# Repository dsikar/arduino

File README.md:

LCD multinode proof of concept
==============

Connect an LCD to a master node, plus a 3 node selector resistor ladder, to a slave node hooked up to a thermistor (LM35).  

This proof-of-concept builds on the Arduino Due to an Arduino Uno I<sup>2</sup>C protocol communication as described in this other GitHub [repository](https://github.com/dsikar/due-uno-i2c). A real life implementation can be found [here](https://github.com/dsikar/arduino/tree/master/lcd-multinode-master-pidx3).

Now there is an LCD plus a resistor ladder added to the master node and a thermistor added to the slave node. Temperature is set on the master node and, while no PID over is hooked up, read from the slave node.

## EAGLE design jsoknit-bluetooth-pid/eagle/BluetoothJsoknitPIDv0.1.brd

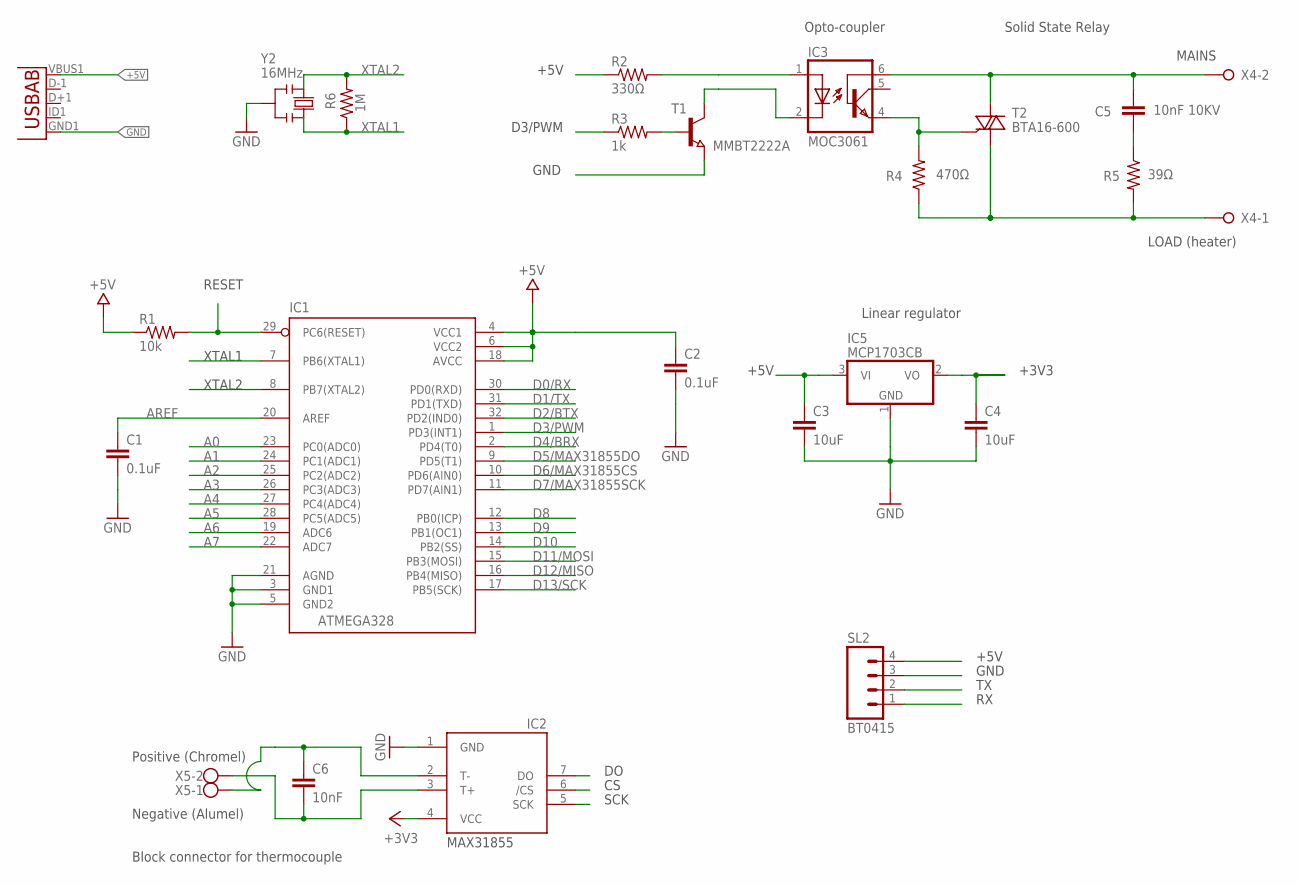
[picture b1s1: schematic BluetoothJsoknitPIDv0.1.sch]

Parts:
C1, C2: 0.1uF; C0805
C3, C4: 10uF; C0805
C5: 10nF 10KV; C050-025X075
C6: 10nF; C0805
IC1: ATMEGA328; QFP032
IC2: MAX6675; SO08
IC3: MOC3061; DIL6-SMD
IC5: MCP1703CB; SOT23
R1: 10k; M0805
R2: 330Ω; M0805
R3: 1k; M0805
R4: 470Ω; 0207/10
R5: 39Ω; 0207/10
R6: 1M; M0805
SL2: BT0415; 04P
T1: MMBT2222A; SOT23
T2: BTA16-600; TO220BV
U$4: USB-AB""; USB-AB-MICRO-SMD_V02_BOSS
X4: W237-02P; W237-132
X5: W237-102
Y2: 16MHz; RESONATOR

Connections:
+3V3: C4.1, IC2.4 (VCC), IC5.2 (VO)
+5V: C2.1, C3.1, IC1.4 (VCC1), IC1.6 (VCC2), IC1.18 (AVCC), IC5.3 (VI), R1.1, R2.1, SL2.4, U$4.VBUS1 (VBUS)
A0: IC1.23 (PC0(ADC0))
A1: IC1.24 (PC1(ADC1))
A2: IC1.25 (PC2(ADC2))
A3: IC1.26 (PC3(ADC3))
A4: IC1.27 (PC4(ADC4))
A5: IC1.28 (PC5(ADC5))
A6: IC1.19 (ADC6)
A7: IC1.22 (ADC7)
AREF: C1.1, IC1.20 (AREF)
D0/RX: IC1.30 (PD0(RXD))
D1/TX: IC1.31 (PD1(TXD))
D2/BTX: IC1.32 (PD2(IND0)), SL2.2
D3/PWM: IC1.1 (PD3(INT1)), R3.1
D4/BRX: IC1.2 (PD4(T0)), SL2.1
D5/MAX31855DO: IC1.9 (PD5(T1)), IC2.7 (DO)
D6/MAX31855CS: IC1.10 (PD6(AIN0)), IC2.6 (/CS)
D7/MAX31855SCK: IC1.11 (PD7(AIN1)), IC2.5 (SCK)
D8: IC1.12 (PB0(ICP))
D9: IC1.13 (PB1(OC1))
D10: IC1.14 (PB2(SS))
D11/MOSI: IC1.15 (PB3(MOSI))
D12/MISO: IC1.16 (PB4(MISO))
D13/SCK: IC1.17 (PB5(SCK))
GND: C1.2, C2.2, C3.2, C4.2, IC1.3 (GND1), IC1.5 (GND2), IC1.21 (AGND), IC2.1 (GND), IC5.1 (GND), SL2.3, T1.2 (E), U$4.GND1 (GND), Y2.2
LOAD: R4.1, R5.2, T2.T1 (A1), X4.1
MAINS: C5.1, IC3.6 (BAS), T2.T2 (A2), X4.2
MOC3061PIN4: IC3.4 (EMI), R4.2, T2.G
unnamed: IC3.2 (C), T1.3 (C)
unnamed: R3.2, T1.1 (B)
unnamed: IC3.1 (A), R2.2
unnamed: C5.2, R5.1
RESET: IC1.29 (PC6(RESET)), R1.2
T+: C6.2, IC2.3 (T+), X5.2
T-: C6.1, IC2.2 (T-)
T-1: X5.1
XTAL1: IC1.7 (PB6(XTAL1)), R6.1, Y2.3
XTAL2: IC1.8 (PB7(XTAL2)), R6.2, Y2.1

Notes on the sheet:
XTAL1
XTAL2
+5V
D3/PWM
GND
LOAD (heater)
MAINS
Block connector for thermocouple
SCK
Positive (Chromel)
Negative (Alumel)
+3V3
Opto-coupler
Solid State Relay
Linear regulator
MAX31855
RESET

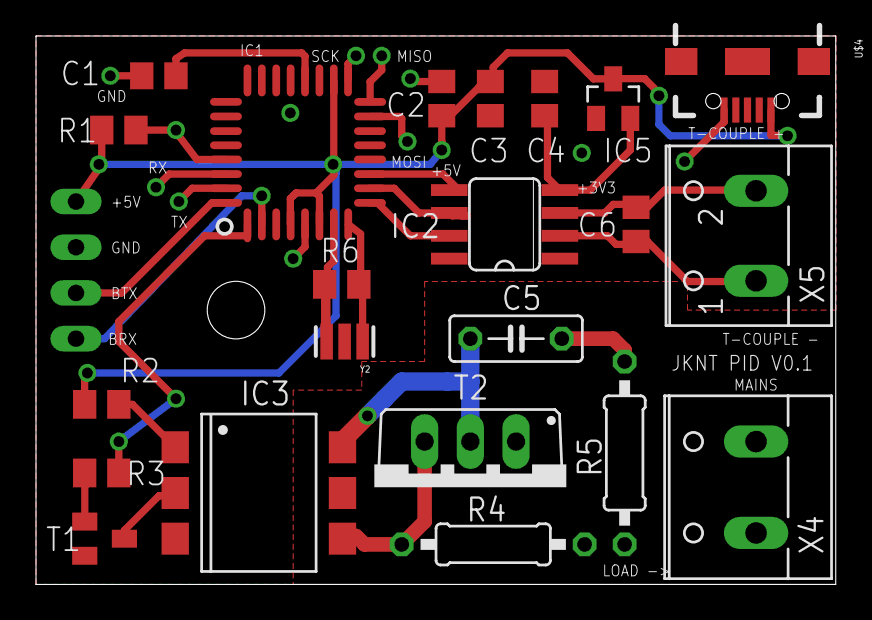
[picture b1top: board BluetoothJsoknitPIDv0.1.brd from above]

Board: 2 copper layers, 44.4 x 30.5 mm, 23 parts (1 on the bottom side), 22 nets.

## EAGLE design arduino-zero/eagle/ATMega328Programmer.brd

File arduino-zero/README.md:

$1 Arduino programmer a.k.a RDNO Zero.
==============

This device provides the following features:  

* Ability to burn a bootloader and upload code to an ATmega328 TQFP-32 device.
* 5 output pins: D0, D1, D11, D12 and D13.  

To burn the bootloader and upload code, [follow these steps] (https://github.com/dsikar/arduino/tree/master/lcd-multinode-master-pidx3#notes-on-configuring-the-arduino-on-a-breadboard), changing the Due board option for Uno, basically turning the ATmega328 TQFP-32 into a feature-limited Uno, hence the name RDNO 0.

Notice that when burning the bootloader, SCK, MOSI, MISO and RESET pins need to be wired. When uploading code, the required pins are RX, TX and RESET. In both cases, Ground and +5V need to be wired.  

Once the code is uploaded, you'll have a very basic Arduino in your hands, and somewhat precarious, given that the chip is secured to board with a crocodile clip, but hey, that is $1's worth of arduino goodness.

The connectors on the board, from left to right, match the SL1 connector in the schematic from top to bottom.

# Gallery

**Burning the bootloader**  
Here we have SCK, MOSI, MISO, RESET, +5V and GND wired    

**Uploading code**  
RX, TX, RESET, +5V and GND wired  

**Blink example**  
SCK, +5V and GND wired, SCK (D13) wired to UNO's D13 to use the on-board LED  

**Bluetooth LED**  
D11, D12, D13, +5V and GND wired, D11 wired to LED, D11 and D12 functioning as RX and TX to [Bluetooth module] (https://github.com/dsikar/jskonit-proof-of-concept)

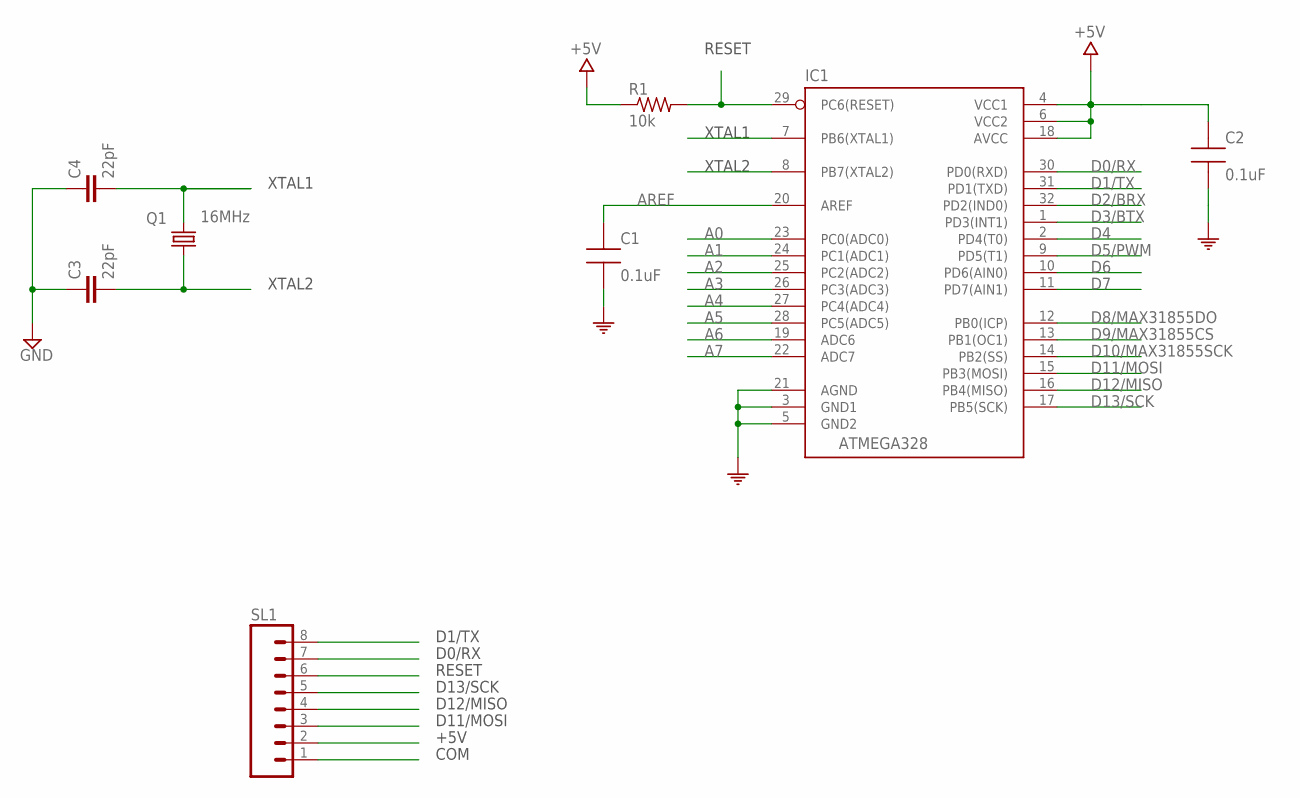
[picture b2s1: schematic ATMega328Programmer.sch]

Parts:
C1, C2: 0.1uF; CAP0805-NP
C3, C4: 22pF; C0805
IC1: ATMEGA328; QFP032
Q1: 16MHz; HC49/S
R1: 10k; M0805
SL1: M08; 08P

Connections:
+5V: C2.1, IC1.4 (VCC1), IC1.6 (VCC2), IC1.18 (AVCC), R1.1, SL1.2
A0: IC1.23 (PC0(ADC0))
A1: IC1.24 (PC1(ADC1))
A2: IC1.25 (PC2(ADC2))
A3: IC1.26 (PC3(ADC3))
A4: IC1.27 (PC4(ADC4))
A5: IC1.28 (PC5(ADC5))
A6: IC1.19 (ADC6)
A7: IC1.22 (ADC7)
AREF: C1.1, IC1.20 (AREF)
COM: C1.2, C2.2, C3.1, C4.1, IC1.3 (GND1), IC1.5 (GND2), IC1.21 (AGND), SL1.1
D0/RX: IC1.30 (PD0(RXD)), SL1.7
D1/TX: IC1.31 (PD1(TXD)), SL1.8
D2/BRX: IC1.32 (PD2(IND0))
D3/BTX: IC1.1 (PD3(INT1))
D4: IC1.2 (PD4(T0))
D5/PWM: IC1.9 (PD5(T1))
D6: IC1.10 (PD6(AIN0))
D7: IC1.11 (PD7(AIN1))
D8/MAX31855DO: IC1.12 (PB0(ICP))
D9/MAX31855CS: IC1.13 (PB1(OC1))
D10/MAX31855SCK: IC1.14 (PB2(SS))
D11/MOSI: IC1.15 (PB3(MOSI)), SL1.3
D12/MISO: IC1.16 (PB4(MISO)), SL1.4
D13/SCK: IC1.17 (PB5(SCK)), SL1.5
RESET: IC1.29 (PC6(RESET)), R1.2, SL1.6
XTAL1: C4.2, IC1.7 (PB6(XTAL1)), Q1.2
XTAL2: C3.2, IC1.8 (PB7(XTAL2)), Q1.1

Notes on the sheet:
XTAL1
XTAL2
RESET
D1/TX
D0/RX
D13/SCK
D12/MISO
D11/MOSI
+5V
COM

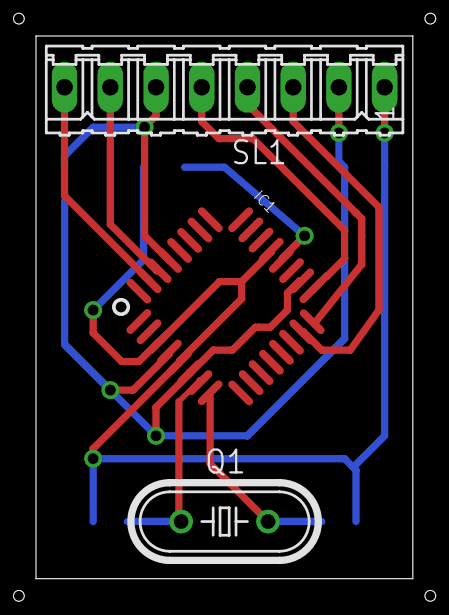
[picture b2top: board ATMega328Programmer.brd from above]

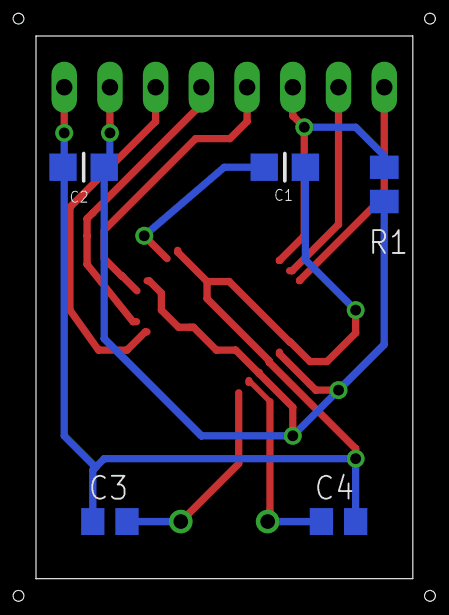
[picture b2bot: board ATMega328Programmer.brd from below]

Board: 2 copper layers, 20.9 x 30.1 mm, 8 parts (5 on the bottom side), 11 nets.

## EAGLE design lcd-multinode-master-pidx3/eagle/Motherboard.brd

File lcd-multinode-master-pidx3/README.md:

LCD master node with breadboard slave node
==============

Now that the Arduino Uno and Due can communicate using the Wire (I2C) library, I'm substituting the Due for an Arduino on a breadboard.  

What we had to start with was:  

Once the Due was swapped, it ended up like this:  

# Notes on configuring the Arduino on a breadboard  

To burn the bootloader and upload sketches to the breadboard Arduino, I followed [these instructions](http://www.arduino.cc/en/Tutorial/ArduinoToBreadboard "http://www.arduino.cc/en/Tutorial/ArduinoToBreadboard") on the arduino.cc website.  

Basically, I wire an Arduino Uno to a breadboard Arduino following this Wiring diagram:  

I worked with two IDEs, versions 1.0.6 and 1.6.4.    

Burning the bootloader threw the error:  

```
(...)
avrdude: Device signature = 0x1e9514
avrdude: Expected signature for ATMEGA328P is 1E 95 0F
         Double check chip, or use -F to override this check.
(...)
```

The error message states that the device signature does not match the expected device signature, as found in configuration file /hardware/tools/avr/etc/avrdude.conf.  
IDE 1.0.6 calls for a change in the last line shown:  

```
#------------------------------------------------------------
# ATmega328P
#------------------------------------------------------------

part
    id			= "m328p";
    desc		= "ATMEGA328P";
    has_debugwire	= yes;
    flash_instr		= 0xB6, 0x01, 0x11;
    eeprom_instr	= 0xBD, 0xF2, 0xBD, 0xE1, 0xBB, 0xCF, 0xB4, 0x00,
			  0xBE, 0x01, 0xB6, 0x01, 0xBC, 0x00, 0xBB, 0xBF,
			  0x99, 0xF9, 0xBB, 0xAF;
    stk500_devcode	= 0x86;
    # avr910_devcode	= 0x;
    signature		= 0x1E 0x95 0xOF;
```

While IDE 1.6.4 calls for a change in the last line shown:  

```
part parent "m328"
    id			= "m328p";
    desc		= "ATmega328P";
    signature		= 0x1e 0x95 0x0F;
```

Once **0x0F** is changed to **0x14**, it is possible to burn the bootloader.  

To upload a sketch to the breadboard Arduino, the wiring diagram changes to:    

Note all IDE settings i.e. board set to Arduino Duemilanove w/ ATmega 328 and programmer set to Arduino as ISP as specified in the [tutorial](http://www.arduino.cc/en/Tutorial/ArduinoToBreadboard "tutorial") plus the ATmega328 must be removed from UNO board.  

When uploading the sketch, the error this time is:  

```
(...)
avrdude: Device signature = 0x1e950f
avrdude: Expected signature for ATMEGA328P is 1E 95 14
         Double check chip, or use -F to override this check.
(...)
```

To fix this new error, in the appropriate IDE dependant section of avrdude.conf file, **0x14** is changed to  **0x0F** then the sketch will upload ok.  

Real life implementation using CADSoft Eagle:

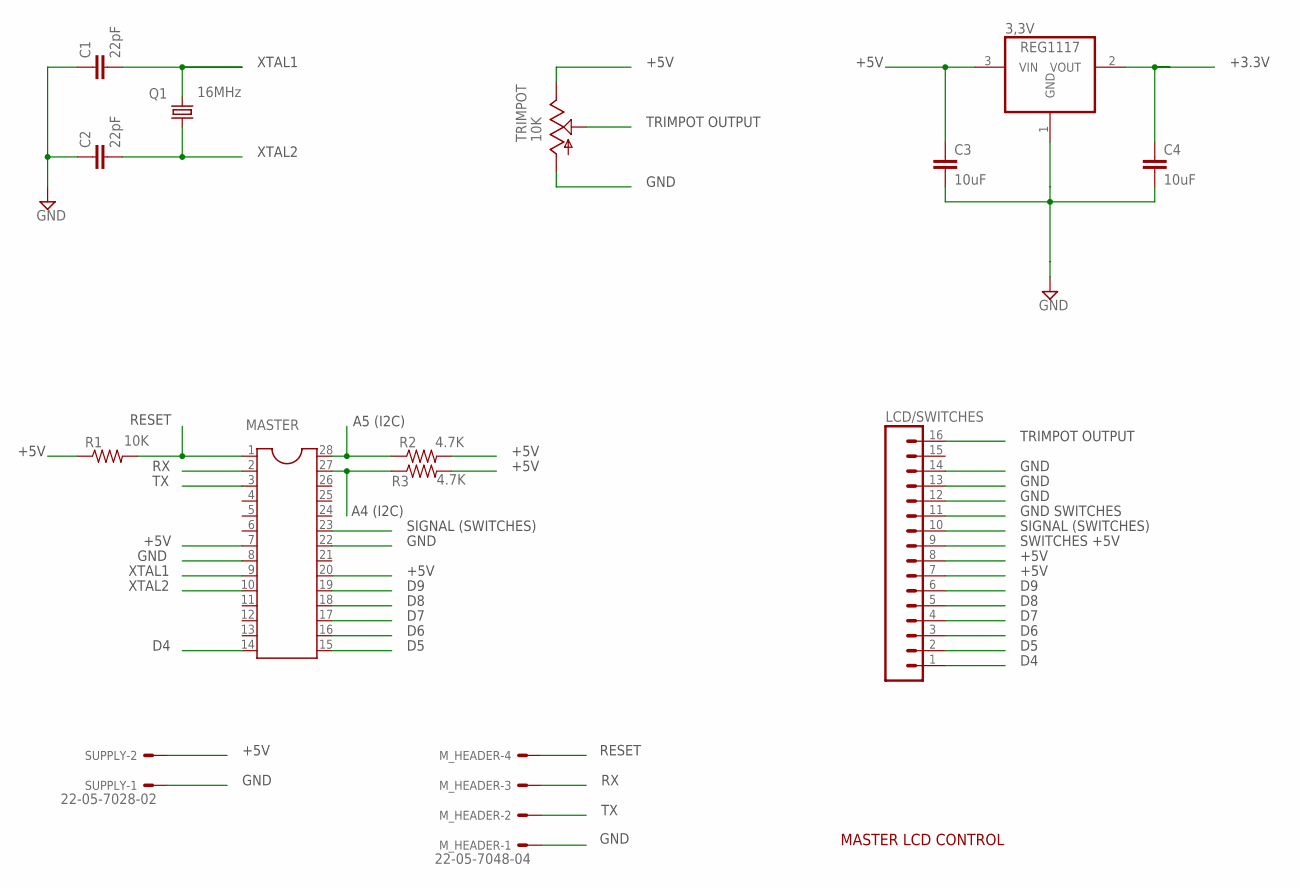
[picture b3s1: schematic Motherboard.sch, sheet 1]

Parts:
3,3V: REG1117; SOT223
C1, C2: 22pF; C0805
C3, C4: 10uF; C0805
LCD/SWITCHES: M16; 16P
MASTER: MASTER NODE; DIL28-3
M_HEADER: 22-05-7048-04; 7395-04
Q1: 16MHz; HC49/S
R1: 10K; M0805
R2, R3: 4.7K; M0805
SUPPLY: 22-05-7028-02; 7395-02
TRIMPOT: 10K; S64W

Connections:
+3.3V: 3,3V.2 (VOUT), C4.1; also elsewhere on the board
+5V: 3,3V.3 (VIN), C3.1, LCD/SWITCHES.7, LCD/SWITCHES.8, LCD/SWITCHES.9, MASTER.7, MASTER.20, R1.1, R2.2, R3.2, SUPPLY.2, TRIMPOT.E; also elsewhere on the board
A4: MASTER.27, R3.1; also elsewhere on the board
A5: MASTER.28, R2.1; also elsewhere on the board
D4: LCD/SWITCHES.1, MASTER.14
D5: LCD/SWITCHES.2, MASTER.15
D6: LCD/SWITCHES.3, MASTER.16
D7: LCD/SWITCHES.4, MASTER.17
D8: LCD/SWITCHES.5, MASTER.18
D9: LCD/SWITCHES.6, MASTER.19
GND: 3,3V.1 (GND), C1.1, C2.1, C3.2, C4.2, LCD/SWITCHES.11, LCD/SWITCHES.12, LCD/SWITCHES.13, LCD/SWITCHES.14, MASTER.8, MASTER.22, M_HEADER.1, SUPPLY.1, TRIMPOT.A; also elsewhere on the board
RESET: MASTER.1, M_HEADER.4, R1.2
RX: MASTER.2, M_HEADER.3
SIGNAL: LCD/SWITCHES.10, MASTER.23
TRIMPOT_OUTPUT: LCD/SWITCHES.16, TRIMPOT.S
TX: MASTER.3, M_HEADER.2
XTAL1: C1.2, MASTER.9, Q1.2
XTAL2: C2.2, MASTER.10, Q1.1

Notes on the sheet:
GND
+5V
TRIMPOT OUTPUT
SIGNAL (SWITCHES)
XTAL1
XTAL2
+3.3V
MASTER LCD CONTROL
A4 (I2C)
A5 (I2C)
RESET
GND SWITCHES
SWITCHES +5V

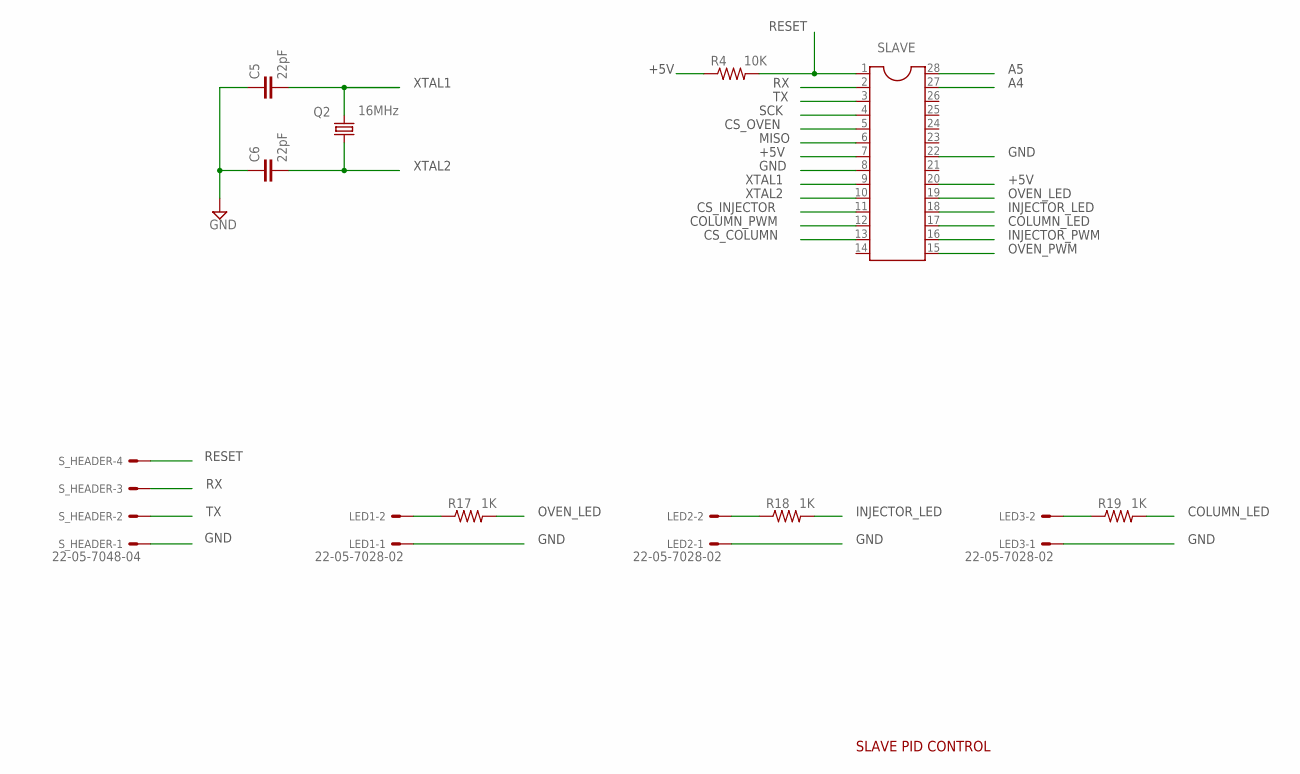
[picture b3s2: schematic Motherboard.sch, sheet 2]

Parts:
C5, C6: 22pF; C0805
LED1, LED2, LED3: 22-05-7028-02; 7395-02
Q2: 16MHz; HC49/S
R4: 10K; M0805
R17, R18, R19: 1K; M0805
SLAVE: DIL28-3
S_HEADER: 22-05-7048-04; 7395-04

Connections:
+5V: R4.1, SLAVE.7, SLAVE.20; also elsewhere on the board
A4: SLAVE.27; also elsewhere on the board
A5: SLAVE.28; also elsewhere on the board
COLUMN_LED: R19.2, SLAVE.17
COLUMN_PWM: SLAVE.12; also elsewhere on the board
CS_COLUMN: SLAVE.13; also elsewhere on the board
CS_INJECTOR: SLAVE.11; also elsewhere on the board
CS_OVEN: SLAVE.5; also elsewhere on the board
GND: C5.1, C6.1, LED1.1, LED2.1, LED3.1, SLAVE.8, SLAVE.22, S_HEADER.1; also elsewhere on the board
INJECTOR_LED: R18.2, SLAVE.18
INJECTOR_PWM: SLAVE.16; also elsewhere on the board
MISO: SLAVE.6; also elsewhere on the board
unnamed: LED2.2, R18.1
unnamed: LED3.2, R19.1
unnamed: LED1.2, R17.1
OVEN_LED: R17.2, SLAVE.19
OVEN_PWM: SLAVE.15; also elsewhere on the board
RESET_SLAVE: R4.2, SLAVE.1, S_HEADER.4
RX_SLAVE: SLAVE.2, S_HEADER.3
SCK: SLAVE.4; also elsewhere on the board
TX_SLAVE: SLAVE.3, S_HEADER.2
XTAL1_SLAVE: C5.2, Q2.2, SLAVE.9
XTAL2_SLAVE: C6.2, Q2.1, SLAVE.10

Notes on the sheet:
+5V
GND
XTAL1
XTAL2
RESET
MISO
SCK
CS_OVEN
CS_INJECTOR
CS_COLUMN
OVEN_LED
INJECTOR_LED
COLUMN_LED
COLUMN_PWM
INJECTOR_PWM
OVEN_PWM
SLAVE PID CONTROL

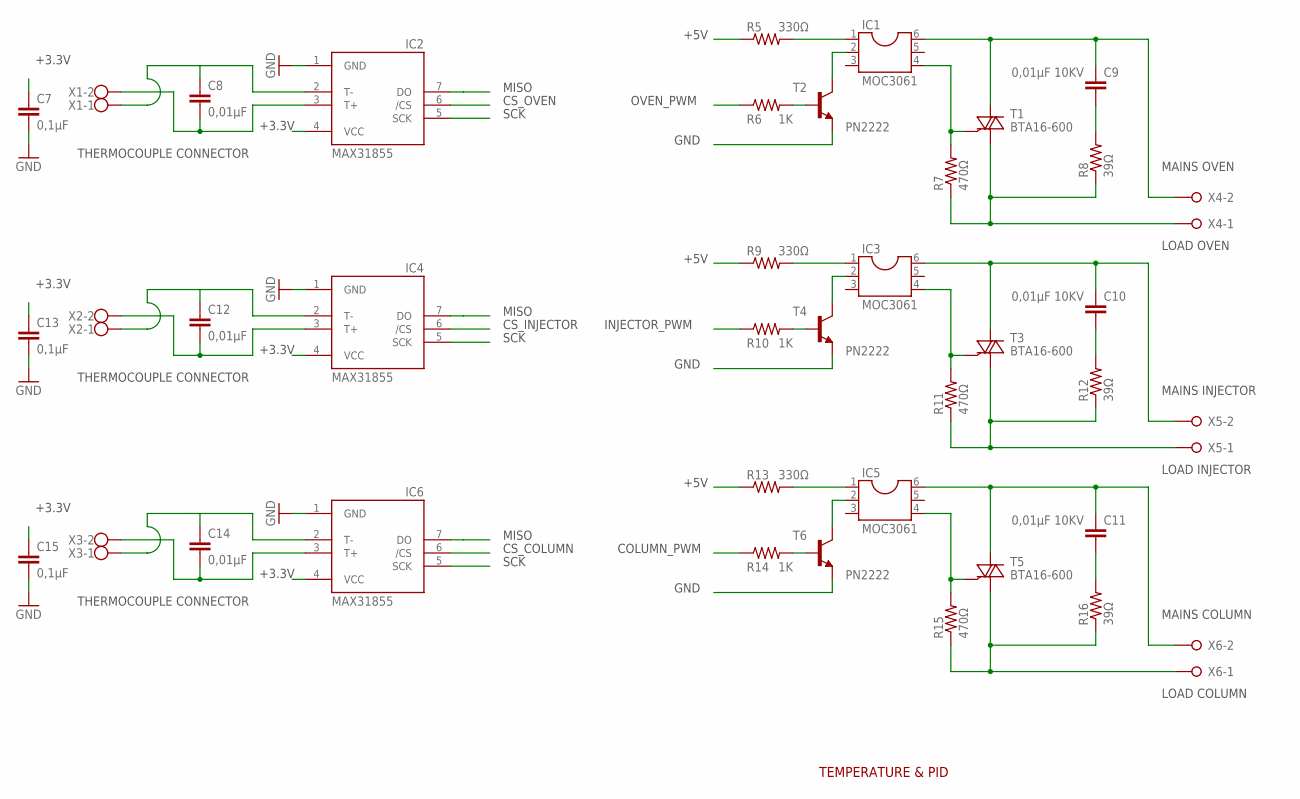
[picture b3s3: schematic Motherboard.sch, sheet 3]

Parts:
C7, C13, C15: 0,1µF; C0805
C8, C12, C14: 0,01µF; C0805
C9, C10, C11: 0,01µF 10KV; C050-025X075
IC1, IC3, IC5: MOC3061; SOCKET-06
IC2, IC4, IC6: MAX31855; SO08
R5, R9, R13: 330Ω; M0805
R6, R10, R14: 1K; M0805
R7, R11, R15: 470Ω; 0207/10
R8, R12, R16: 39Ω; 0207/10
T1, T3, T5: BTA16-600; TO220BV
T2, T4, T6: PN2222; TO92-EBC
X1, X2, X3: W237-102
X4, X5, X6: W237-02P; W237-132

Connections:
+3.3V: C7.1, C13.1, C15.1, IC2.4 (VCC), IC4.4 (VCC), IC6.4 (VCC); also elsewhere on the board
+5V: R5.1, R9.1, R13.1; also elsewhere on the board
COLUMN_PWM: R14.1; also elsewhere on the board
CS_COLUMN: IC6.6 (/CS); also elsewhere on the board
CS_INJECTOR: IC4.6 (/CS); also elsewhere on the board
CS_OVEN: IC2.6 (/CS); also elsewhere on the board
GND: C7.2, C13.2, C15.2, IC2.1 (GND), IC4.1 (GND), IC6.1 (GND), T2.E, T4.E, T6.E; also elsewhere on the board
INJECTOR_PWM: R10.1; also elsewhere on the board
LOAD_COLUMN: R15.1, R16.1, T5.T1 (A1), X6.1
LOAD_INJECTOR: R11.1, R12.1, T3.T1 (A1), X5.1
LOAD_OVEN: R7.1, R8.1, T1.T1 (A1), X4.1
MAINS_COLUMN: C11.1, IC5.6, T5.T2 (A2), X6.2
MAINS_INJECTOR: C10.1, IC3.6, T3.T2 (A2), X5.2
MAINS_OVEN: C9.1, IC1.6, T1.T2 (A2), X4.2
MISO: IC2.7 (DO), IC4.7 (DO), IC6.7 (DO); also elsewhere on the board
unnamed: C10.2, R12.2
unnamed: IC3.2, T4.C
unnamed: R10.2, T4.B
unnamed: C9.2, R8.2
unnamed: IC1.2, T2.C
unnamed: R6.2, T2.B
unnamed: IC1.1, R5.2
unnamed: IC3.1, R9.2
unnamed: IC1.4, R7.2, T1.G
unnamed: IC3.4, R11.2, T3.G
unnamed: C11.2, R16.2
unnamed: IC5.2, T6.C
unnamed: R14.2, T6.B
unnamed: IC5.1, R13.2
unnamed: IC5.4, R15.2, T5.G
OVEN_PWM: R6.1; also elsewhere on the board
SCK: IC2.5 (SCK), IC4.5 (SCK), IC6.5 (SCK); also elsewhere on the board
T+: C8.2, IC2.3 (T+), X1.2
T+1: C12.2, IC4.3 (T+), X2.2
T+2: C14.2, IC6.3 (T+), X3.2
T-: C8.1, IC2.2 (T-), X1.1
T-1: C12.1, IC4.2 (T-), X2.1
T-2: C14.1, IC6.2 (T-), X3.1

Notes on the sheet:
+5V
OVEN_PWM
GND
LOAD OVEN
MAINS OVEN
MISO
CS_OVEN
SCK
THERMOCOUPLE CONNECTOR
+3.3V
INJECTOR_PWM
LOAD INJECTOR
MAINS INJECTOR
COLUMN_PWM
LOAD COLUMN
MAINS COLUMN
CS_INJECTOR
CS_COLUMN
TEMPERATURE & PID

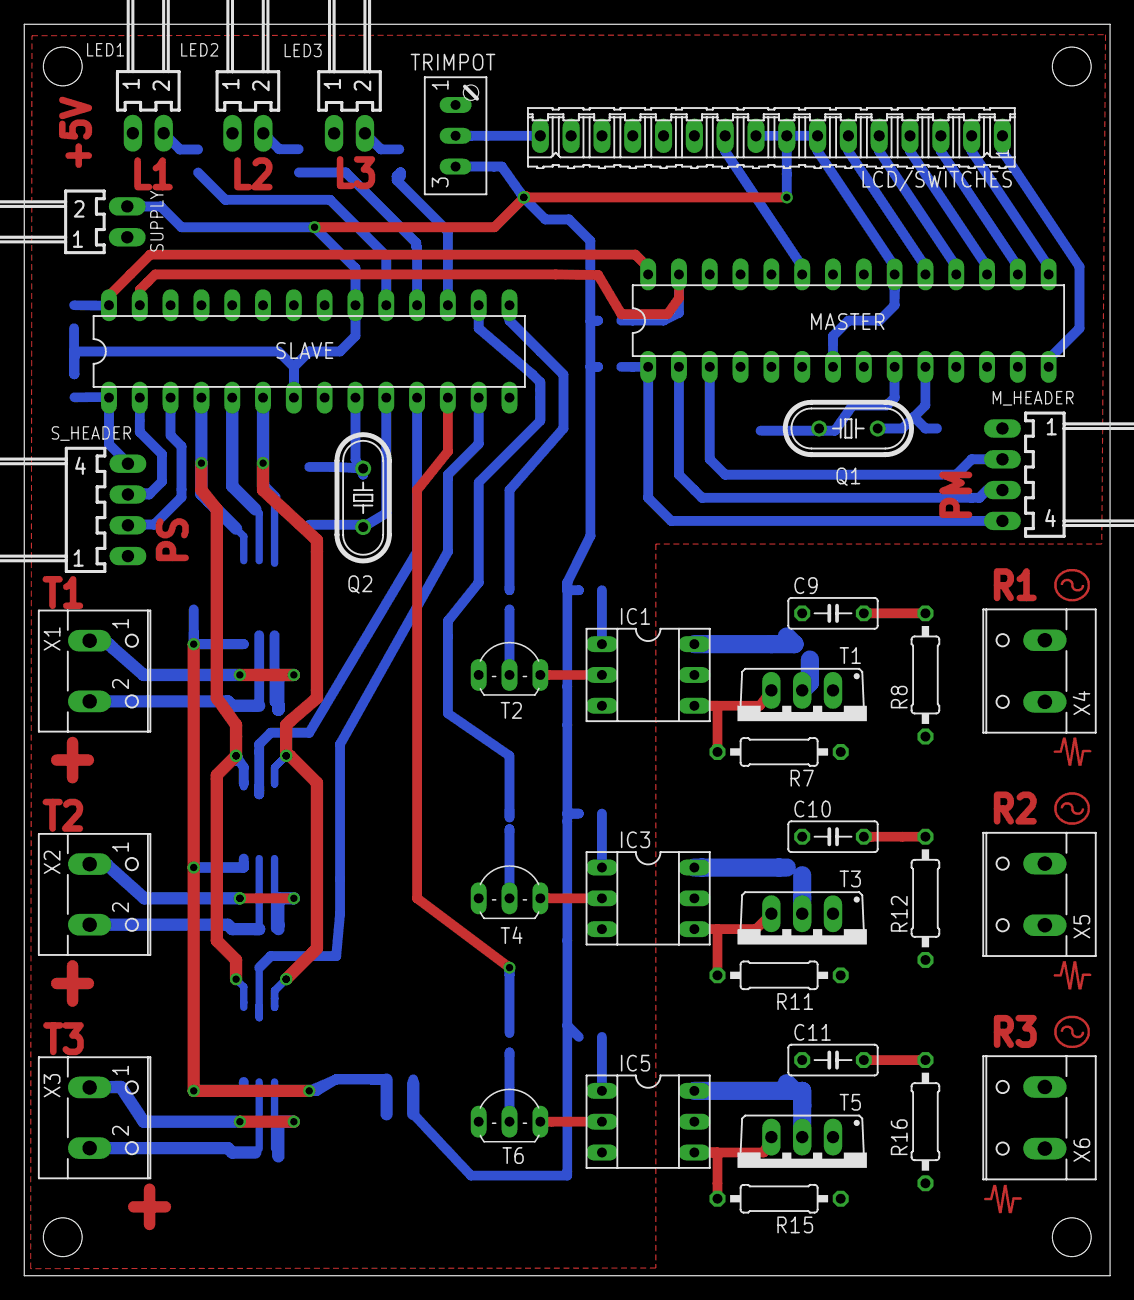
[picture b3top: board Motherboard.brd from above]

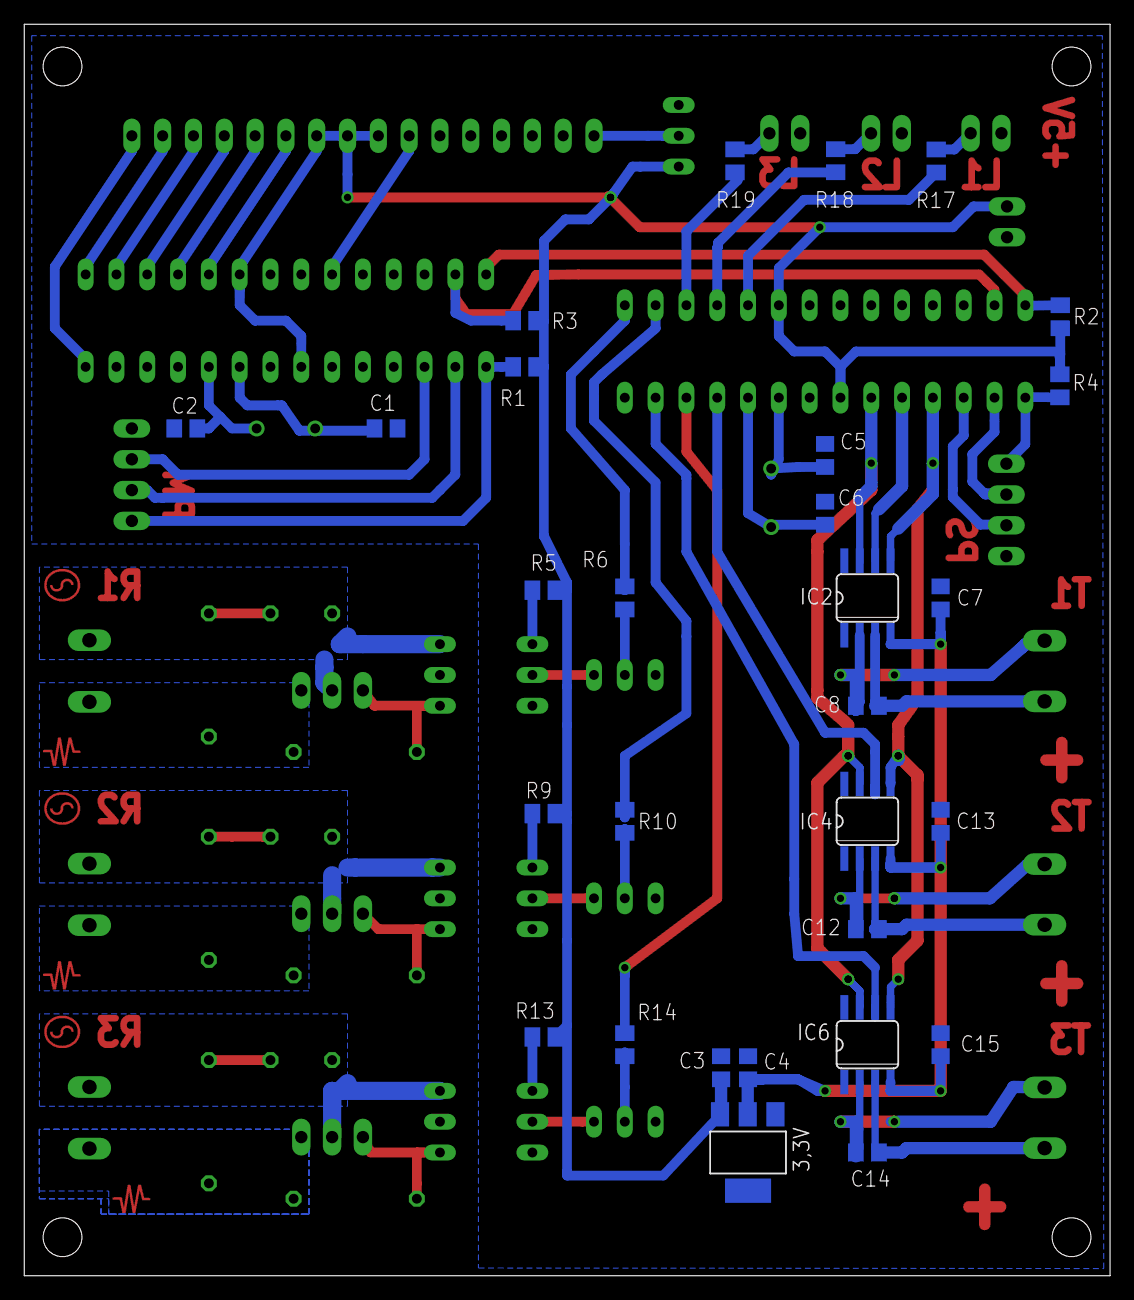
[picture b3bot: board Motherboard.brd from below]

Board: 2 copper layers, 89.5 x 103.2 mm, 65 parts (29 on the bottom side), 64 nets.

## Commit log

2016-03-28 Initial commit.
2016-03-28 Added sketch.
2016-03-30 Added LM35 thermistor.
2016-03-31 Multinode slave sketch.
2016-04-01 Added LM35 thermistor to the slave node.
2016-04-01 Moved README.md to top level.
2016-04-01 Added todos.
2016-04-01 x compatibility todo.
2016-04-02 I2C bit shifting.
2016-04-02 I2C bit shifting on slave.
2016-04-02 More info.
2016-04-02 Typo.
2016-04-02 Writing slave node temp to master node LCD.
2016-04-03 Updated slave node.
2016-04-03 Added master node bit shifting send.
2016-04-03 Cleanup.
2016-04-04 Added slave node with PID.
2016-04-04 Tweaks.
2016-04-05 Added function comments.
2016-04-07 Hack to make master node work on Due boards.
2016-04-07 Added library info.
2016-04-14 Added branch.
2016-04-14 Uno version tweak.
2016-04-23 Running three PID controllers on a single ATMEGA328.
2016-04-23 Added reference.
2016-04-25 Adding jason parser.
2016-04-25 Adding json parser tests.
2016-04-25 Added json parser to slave.
2016-04-25 Formatting serial prints.
2016-04-25 Formatted serial prints.
2016-04-26 More cases.
2016-04-27 Added I2C delays.
2016-04-27 Increased delay.
2016-04-27 I2C delays only if Serial Monitor debugging.
2016-04-27 General variable name cleanup.
2016-04-27 More cleaning up.
2016-04-27 Magic number removal.
2016-04-27 Human readable variable names.
2016-04-28 Now using Peter Easton's MAX31855 library.
2016-04-28 Fixed index.
2016-04-28 Debugging.
2016-05-02 Arduino breadboard documentation.
2016-05-03 Added libdef.h.
2016-05-03 Added LED visual checks.
2016-05-04 Added delay(100); statements to make it work between UNOs.
2016-05-04 Cleaned up redundant comments.
2016-05-04 Tweaking delays and Wire.write to make it happen.
2016-05-05 Changing LCD pins.
2016-05-14 Changed pins.
2016-05-24 Changed LED logic.
2016-06-12 Added schematics and box stl files.
2016-06-13 Added Arduino Zero.
2016-06-13 More snake oil.
2016-06-13 More documentation.
2016-06-15 Added Bluetooth example sketch.
2016-06-17 Tweaked temperature.
2016-06-27 Added board image to markdown.
2016-06-27 More Jsoknit goodness.
2017-10-19 Addressable LEDs
2017-12-06 Surplus to requirements
2019-01-18 Added schematic pdf
2019-01-23 initial u8g2 based lib commit
2019-01-24 Added todos
2019-01-25 Added ArduinoISP
2019-01-25 Arduino MEGA2560 ISP sketch
    Run on mega before using "Arduino as ISP" programmer and "Upload using programmer" option
2019-01-27 Added lookup table generators
2019-01-28 Moved variables to program memory
2019-01-28 Added distances table
2019-01-29 LCD demos
2019-01-29 Renamed sketch.
2019-01-29 Added timer interrupts
2019-01-30 Added pin definition header file
2019-01-30 Plumbing
2019-01-31 Adding defines
2019-01-31 Added direction
2019-02-04 Added notes on flashing
2019-02-04 Added table
2019-02-13 checkpoint
2019-02-13 v0.01
2019-02-13 Added v0.02 roadmap
2019-02-17 Dev merge checkpoint
2019-02-17 Checkpoint - broken
2019-02-17 Added EEPROM read/write configuration
2019-02-17 dev version v0.02
2019-02-17 Leftovers.
2019-02-18 UNO CRC Check
2019-02-18 Implement prog mode state machine
2019-02-20 Added CRC check self-corrupting-break-and-fix proof-of-concept
2019-02-20 Added programmed mode
2019-02-21 Trying CRC8
2019-02-23 Added faux CRC - enough EEPROM storage to backup and compare.
2019-02-23 Added memory integrity check
2020-01-05 Arduino ISP example
2020-01-05 Added Arduino ISP hookup photo
2020-02-01 Typo
2021-01-16 Modified for timing-belt systems
2021-01-18 Adjusted speed entries.
2021-01-18 Updated steps/mm
2021-01-18 Updated version
2021-01-18 Adjusted steps per millimiter
2021-06-03 modified end stop polarity
2021-08-07 Added 53cm range
2021-08-07 Added case for 50 steps/revolution
2021-08-07 New tables
2021-08-07 Changed range, steps/mm ratio
2021-08-07 Adjusted tables, changed frequency array to int data type
2021-08-07 Changed frequencies data type
2021-08-07 Changed initial value of timer1
2021-08-09 Changed half_frequency data type to uint32
2021-08-11 Using pgm_read_dword to read frequencies
2021-08-11 Removed redundant semicolon
2021-08-15 Set distance array to 50,4cm
2022-11-10 Using reduction gears
2022-11-11 Increased course to 32cm, modified steps / mm ratio, for GT2 timing belt.
2022-11-12 Starting at 1cm/m
2023-10-13 Changed DIRECTION_PIN polarity
2023-10-13 Removed duplicate 16mm entry
2023-10-13 Added speeds < 1cm/m
2023-10-14 Removed 0.50cm/m
2023-10-14 Steps of 2cm/min between 16 and 14
2023-10-15 Deleted jupyter notebook named with underscores, as google lab prefers hyphens.
2023-10-17 Speeds starting from 1cm/min
2023-10-17 Adding LCDData.h
2023-10-18 Limiting distance to 27cm
2023-10-18 Distance 31cm
2023-10-18 Speeds 24, 26, 28 and 30cm/min.
2023-10-18 Speeds 24 and 30cm/min
2023-10-25 Added 27cm/min dip coater Alexandre
2024-10-13 Removed duplicate entry for 16,00cm
